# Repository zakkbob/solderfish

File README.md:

# Solderfish
My first PCB! It has a button and some LEDs :O

# Schematic
It's very simple, when the button is pressed, the LEDs _should_ turn on, and then the potentiometer will change the brightness.

# PCB
Also, it's supposed to look like a fish.

# Simulation
Here is the [Falstad Simulation](https://www.falstad.com/circuit/circuitjs.html?ctz=CQAgjCAMB0l3BWcMBMcUHYMGZIA4UA2ATmIxAUgpABZsKBTAWjDACgBncYlEbXzL35QRAMwCGAGw4M2AN268wGQor68qVGlSSao0BG2U0Qg9eqpgUecMjj7+YPPBev6AJQYcAlhwAu4gB2AMayYIRCeCbC2FEgxKq8ACYMEgCukn5MkgxJtnowkOzhvDQ0NsJlNgmmICnpmdm5+SKF7ABOtOXgKl3VqlTYuGydsSY1Yz0DfMMA7mrKiRhKvZBs82aLpsvg1lDr2yuqk1tr8ye9VVP781cxccJnFiDOfAi8r0-Y7y+DP48Hb5CSLRDRsIA)

# Features
- Low power! Only 3V
- Contains the [Hacklet](hacklet.hackclub.com) logo :O (My first YSWS)
- Random bits of text I added
- Super cool fish shape

# BOM
| Value | Qty | Reference | Footprint |
| ----- | --- | --------- | --------- |
| Battery_Cell | 1 | BT1 | Battery:BatteryHolder_Keystone_3034_1x20mm | 
| LED | 2 | D1,D2 | LED_THT:LED_D5.0mm | 
| R | 2 | R1,R2 | Resistor_THT:R_Axial_DIN0207_L6.3mm_D2.5mm_P7.62mm_Horizontal | 
| SW_Push | 1 | SW1 | Button_Switch_THT:SW_PUSH_6mm |
| R_Potentiometer | 1 | RV1 | Potentiometer_THT:Potentiometer_Vishay_T73YP_Vertical |

Made by @zakkbob on slack :D

Made for [Solder](https://solder.hackclub.com), a [Hack Club](https://hackclub.com) program where you make your first circuit board and get a kit of electronics to assemble it for free!

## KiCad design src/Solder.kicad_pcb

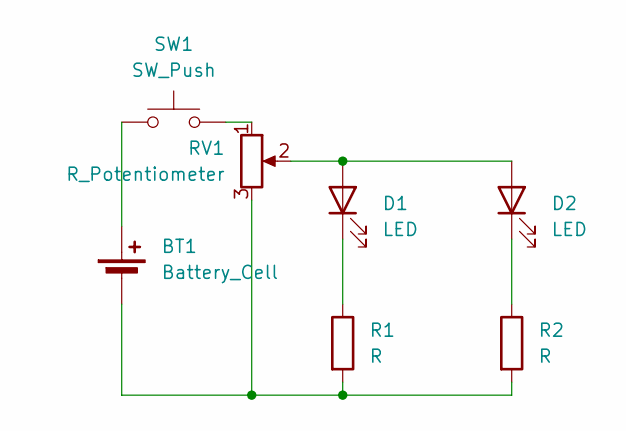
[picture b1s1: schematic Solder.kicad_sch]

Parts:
BT1: Battery_Cell; BatteryHolder_Keystone_3034_1x20mm
D1, D2: LED; LED_D5.0mm
R1, R2: R; R_Axial_DIN0207_L6.3mm_D2.5mm_P7.62mm_Horizontal
RV1: R_Potentiometer; Potentiometer_Vishay_T73YP_Vertical
SW1: SW_Push; SW_PUSH_6mm

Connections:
unnamed: BT1.1 (+), SW1.1
unnamed: BT1.2 (-), R1.2, R2.2, RV1.3
unnamed: D1.2 (A), D2.2 (A), RV1.2
unnamed: D1.1 (K), R1.1
unnamed: D2.1 (K), R2.1
unnamed: RV1.1, SW1.2

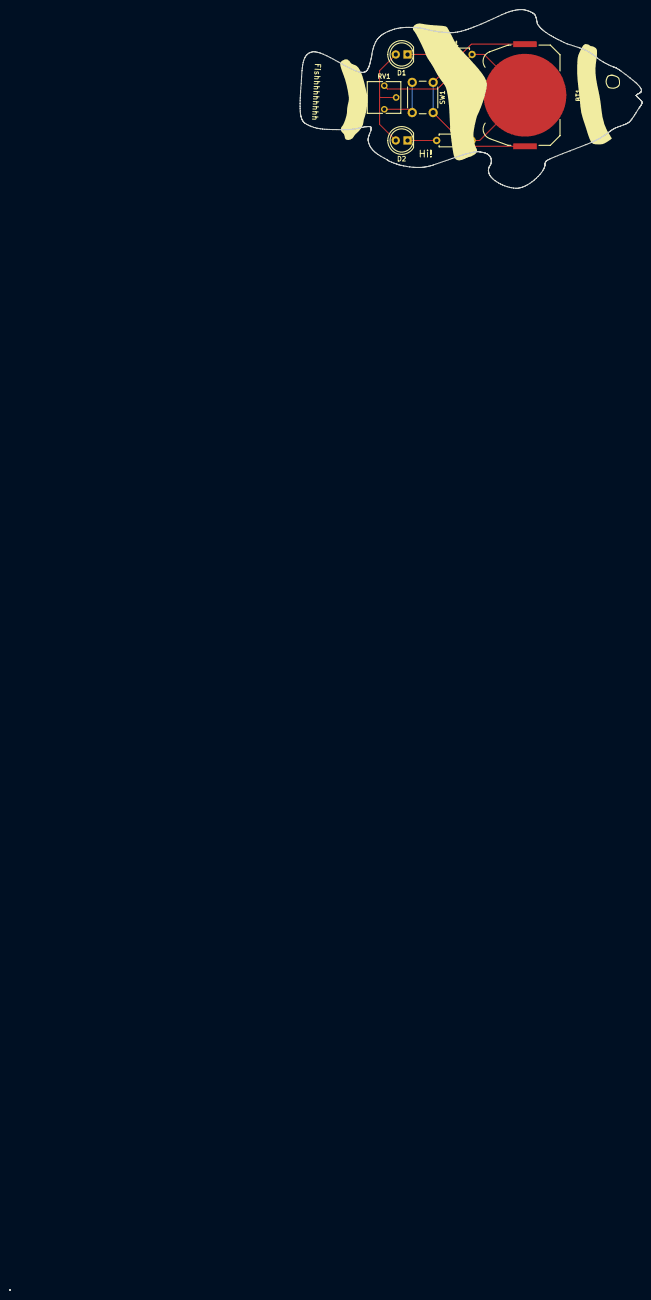
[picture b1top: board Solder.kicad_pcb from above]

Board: 2 copper layers, 73.5 x 38.4 mm, 7 parts (0 on the bottom side), 6 nets.

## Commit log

2025-06-02 Create LICENSE
2025-06-02 Unignore license
2025-06-02 Add random bits
2025-06-02 More random text... (hopefully not too small to print)
2025-06-02 add ground pour
2025-06-02 Ground fill EVERYTHING
2025-06-02 Keychain Hole :D
2025-06-03 Finished? :D
2025-06-03 Moved text
2025-06-03 Add a button
2025-06-03 Fix ground fill
2025-06-03 Finish schematic
2025-06-03 Add images
2025-06-03 Add proper .gitignore
2025-06-03 Restructure
2025-06-29 Add decoration
2025-06-29 move back graphics to B.Silkscreen (not B.Cu)
2025-06-29 Remove unconnected trace
2025-06-29 Update photos
2025-06-29 Add more features!!
2025-06-30 Fix potentiometer wiring
